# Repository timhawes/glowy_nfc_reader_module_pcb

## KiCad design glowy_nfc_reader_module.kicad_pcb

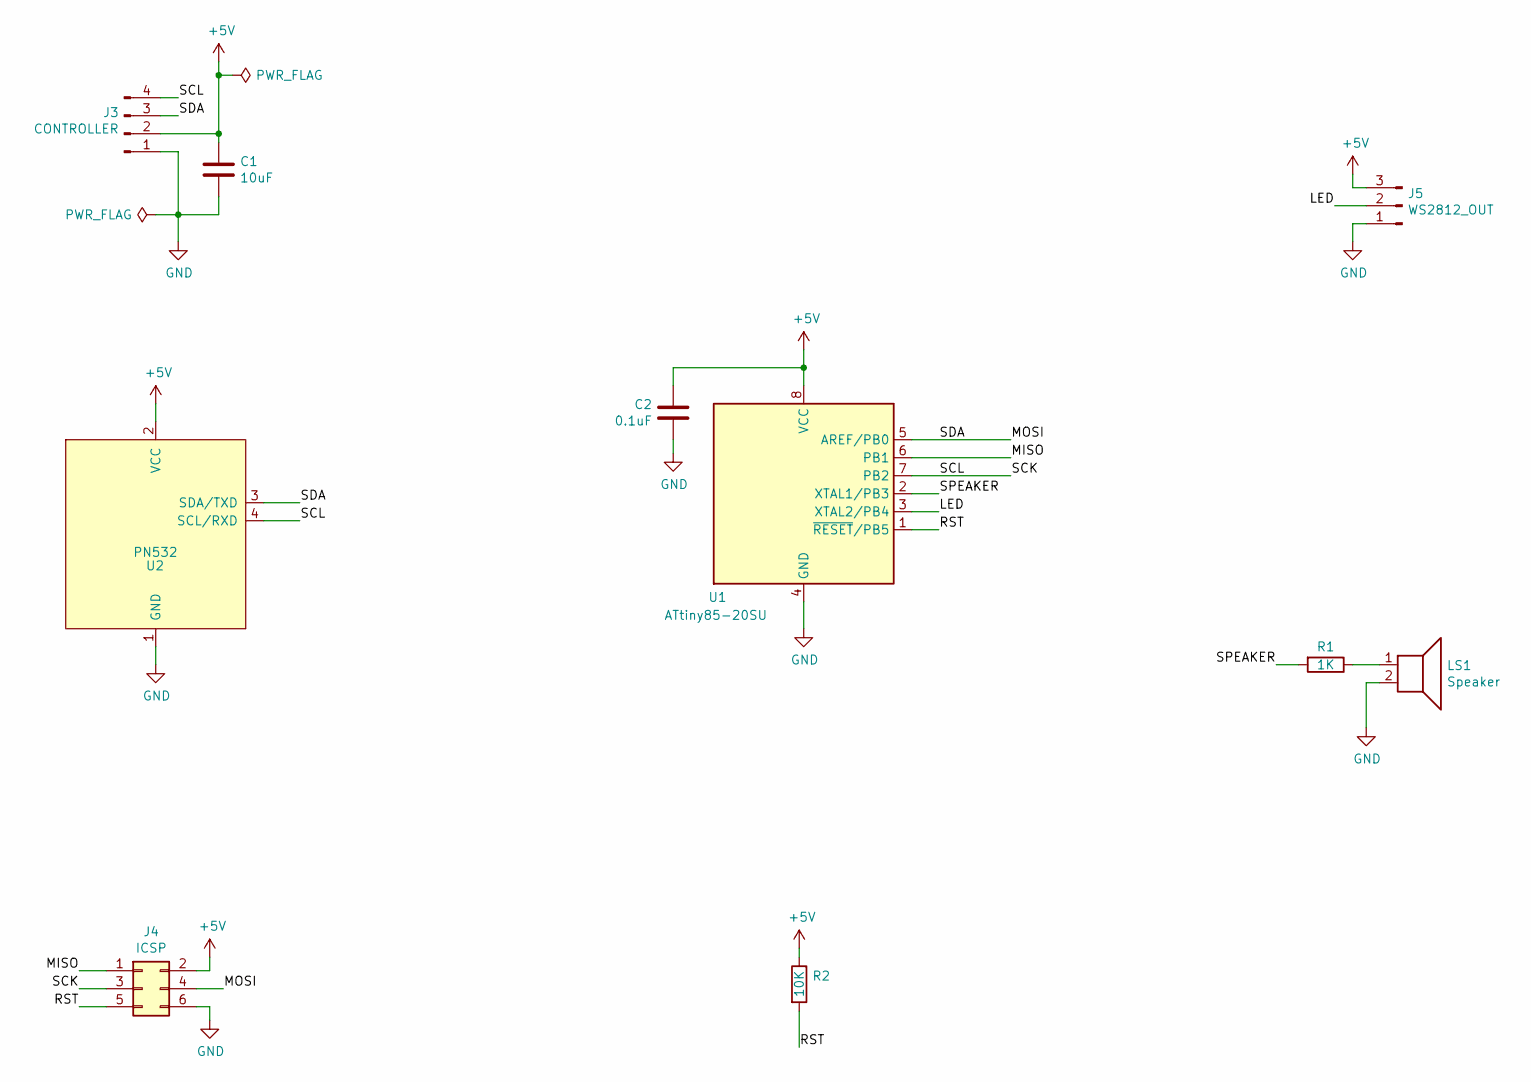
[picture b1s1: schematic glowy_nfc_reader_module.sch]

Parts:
C1: 10uF; C_0805_2012Metric
C2: 0.1uF; C_0603_1608Metric
J3: CONTROLLER; Solder_Connection_4way_with_cable_tie
J4: ICSP; PinHeader_2x03_P2.54mm_Vertical
J5: WS2812_OUT; Solder_Connection_3way
LS1: Speaker; Buzzer_Murata_PKMCS0909E4000-R1
R1: 1K; R_0603_1608Metric
R2: 10K; R_0603_1608Metric
U1: ATtiny85-20SU; SOIJ-8_5.3x5.3mm_P1.27mm
U2: PN532; ELECHOUSE_PN532_V4_USART_I2C

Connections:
+5V: C1.1, C2.2, J3.2, J4.2, J5.3, R2.1, U1.8 (VCC), U2.2 (VCC)
/LED: J5.2, U1.3 (XTAL2/PB4)
/MISO: J4.1, U1.6 (PB1)
/MOSI: J3.3, J4.4, U1.5 (AREF/PB0), U2.3 (SDA/TXD)
/RST: J4.5, R2.2, U1.1 (~RESET~/PB5)
/SCK: J3.4, J4.3, U1.7 (PB2), U2.4 (SCL/RXD)
/SPEAKER: R1.2, U1.2 (XTAL1/PB3)
GND: C1.2, C2.1, J3.1, J4.6, J5.1, LS1.2, U1.4 (GND), U2.1 (GND)
unnamed: LS1.1, R1.1

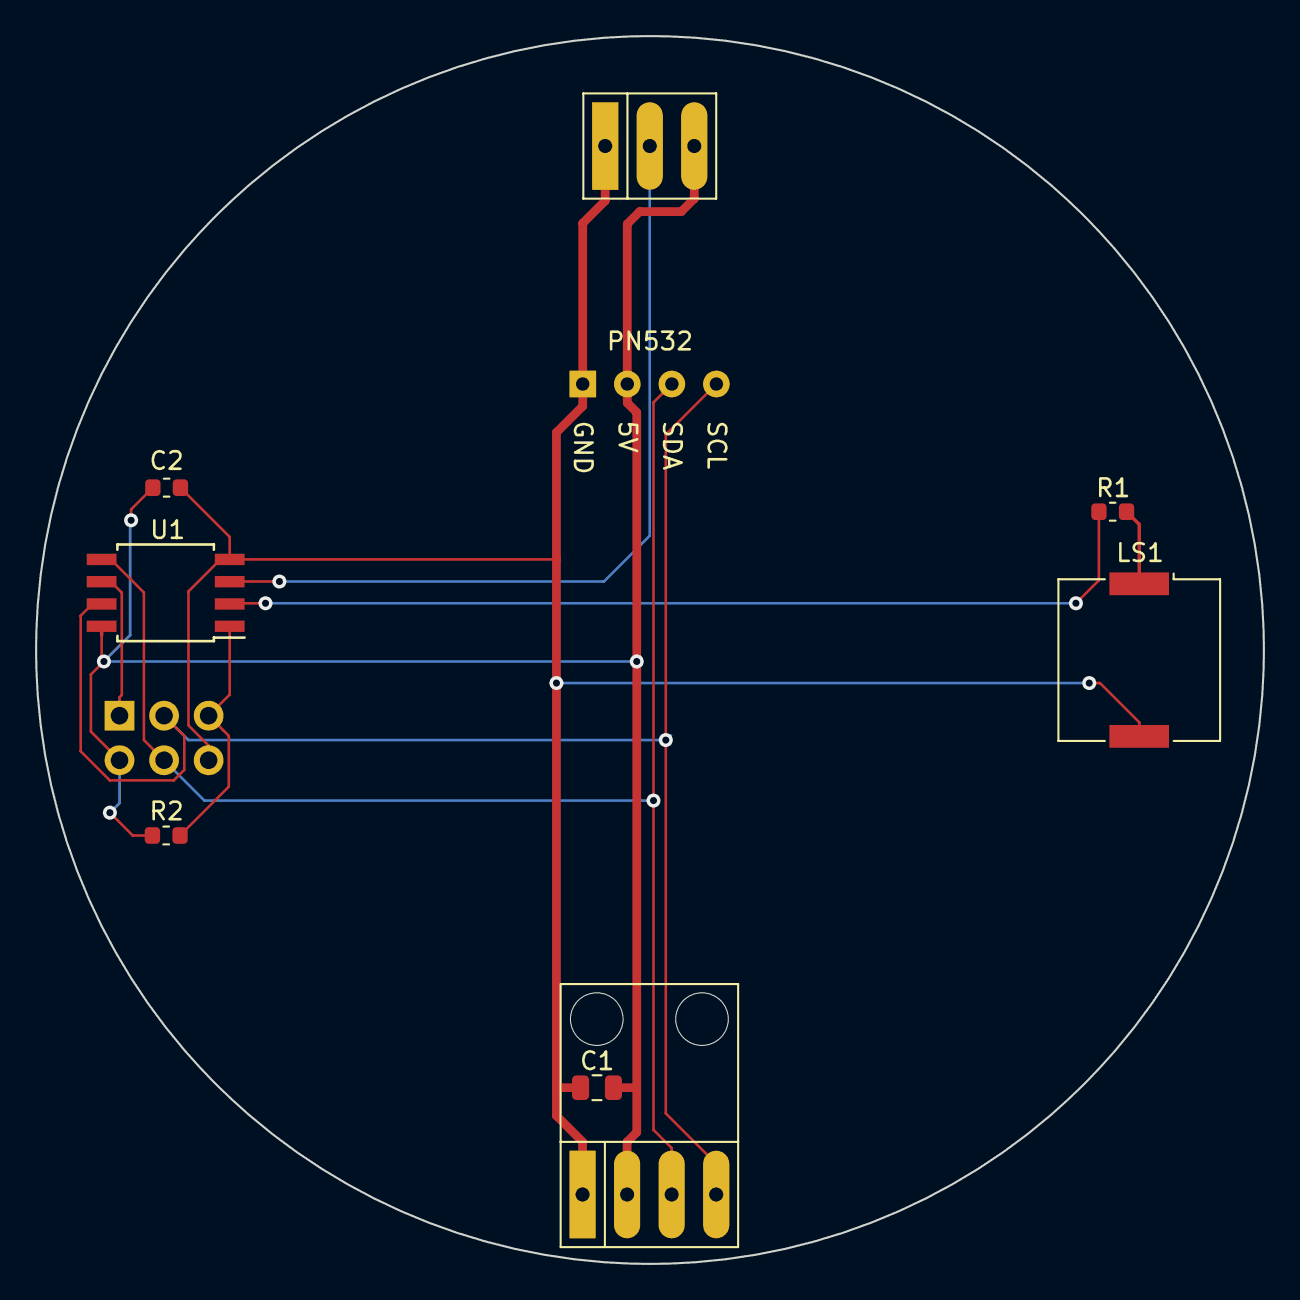
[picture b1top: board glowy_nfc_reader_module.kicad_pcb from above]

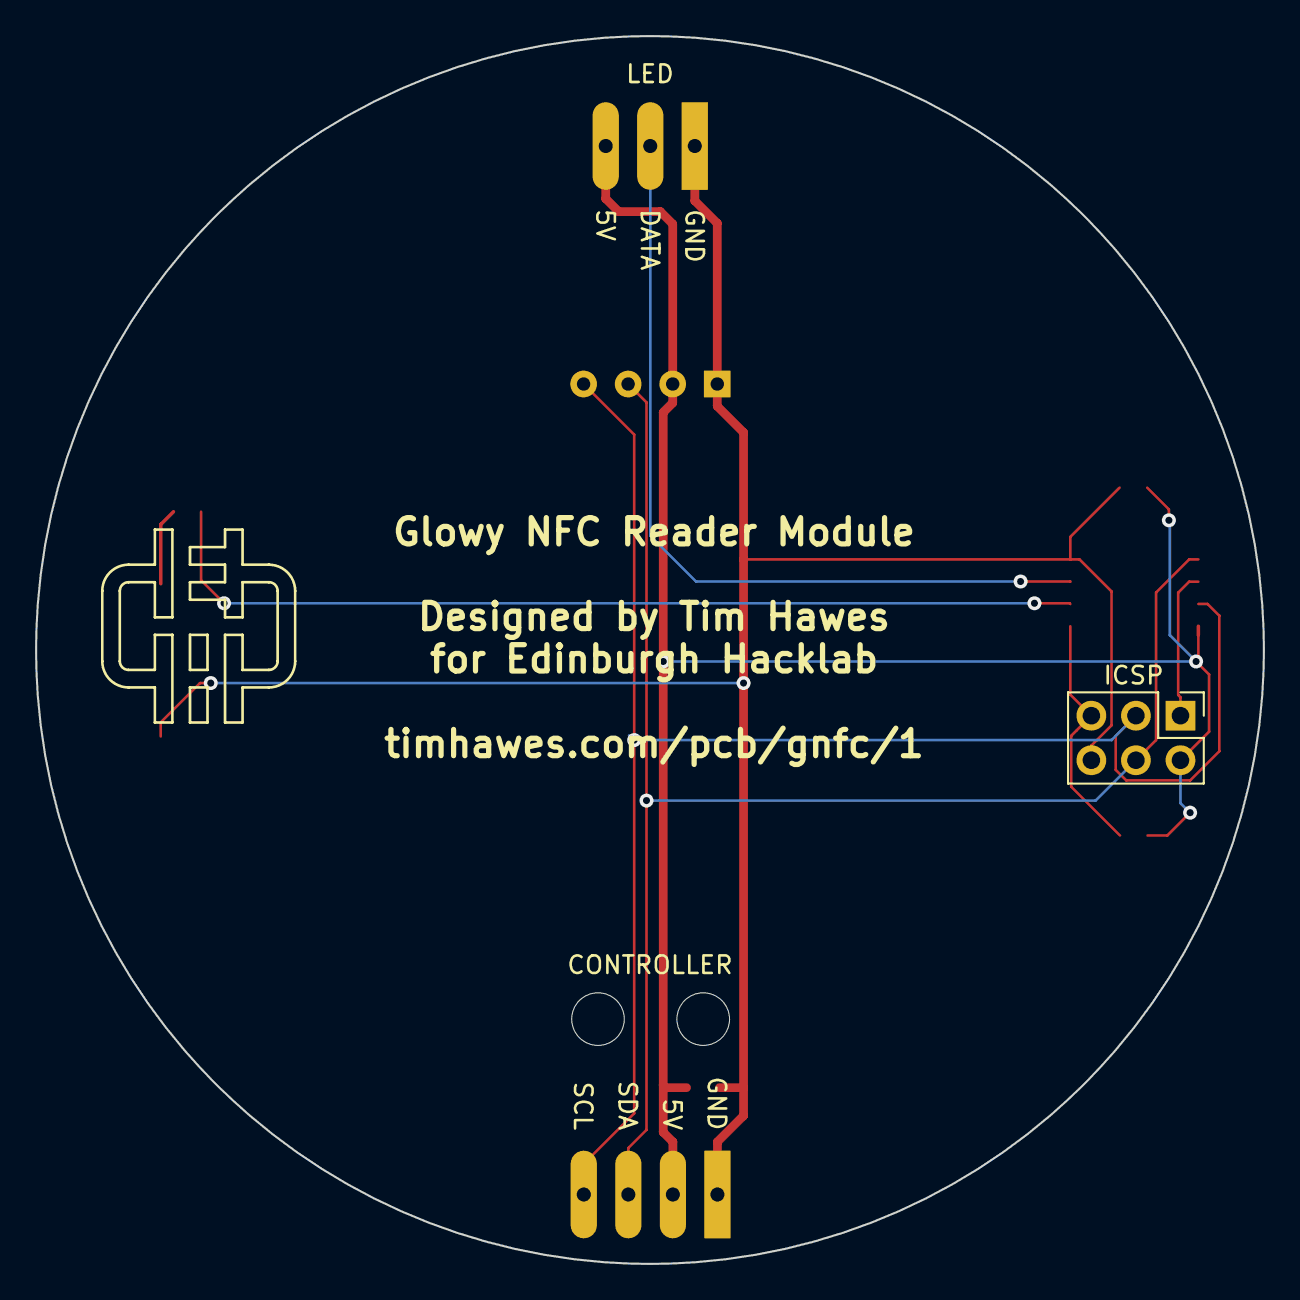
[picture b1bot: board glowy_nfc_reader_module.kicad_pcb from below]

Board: 2 copper layers, 70.0 x 70.0 mm, 10 parts (2 on the bottom side), 9 nets.
